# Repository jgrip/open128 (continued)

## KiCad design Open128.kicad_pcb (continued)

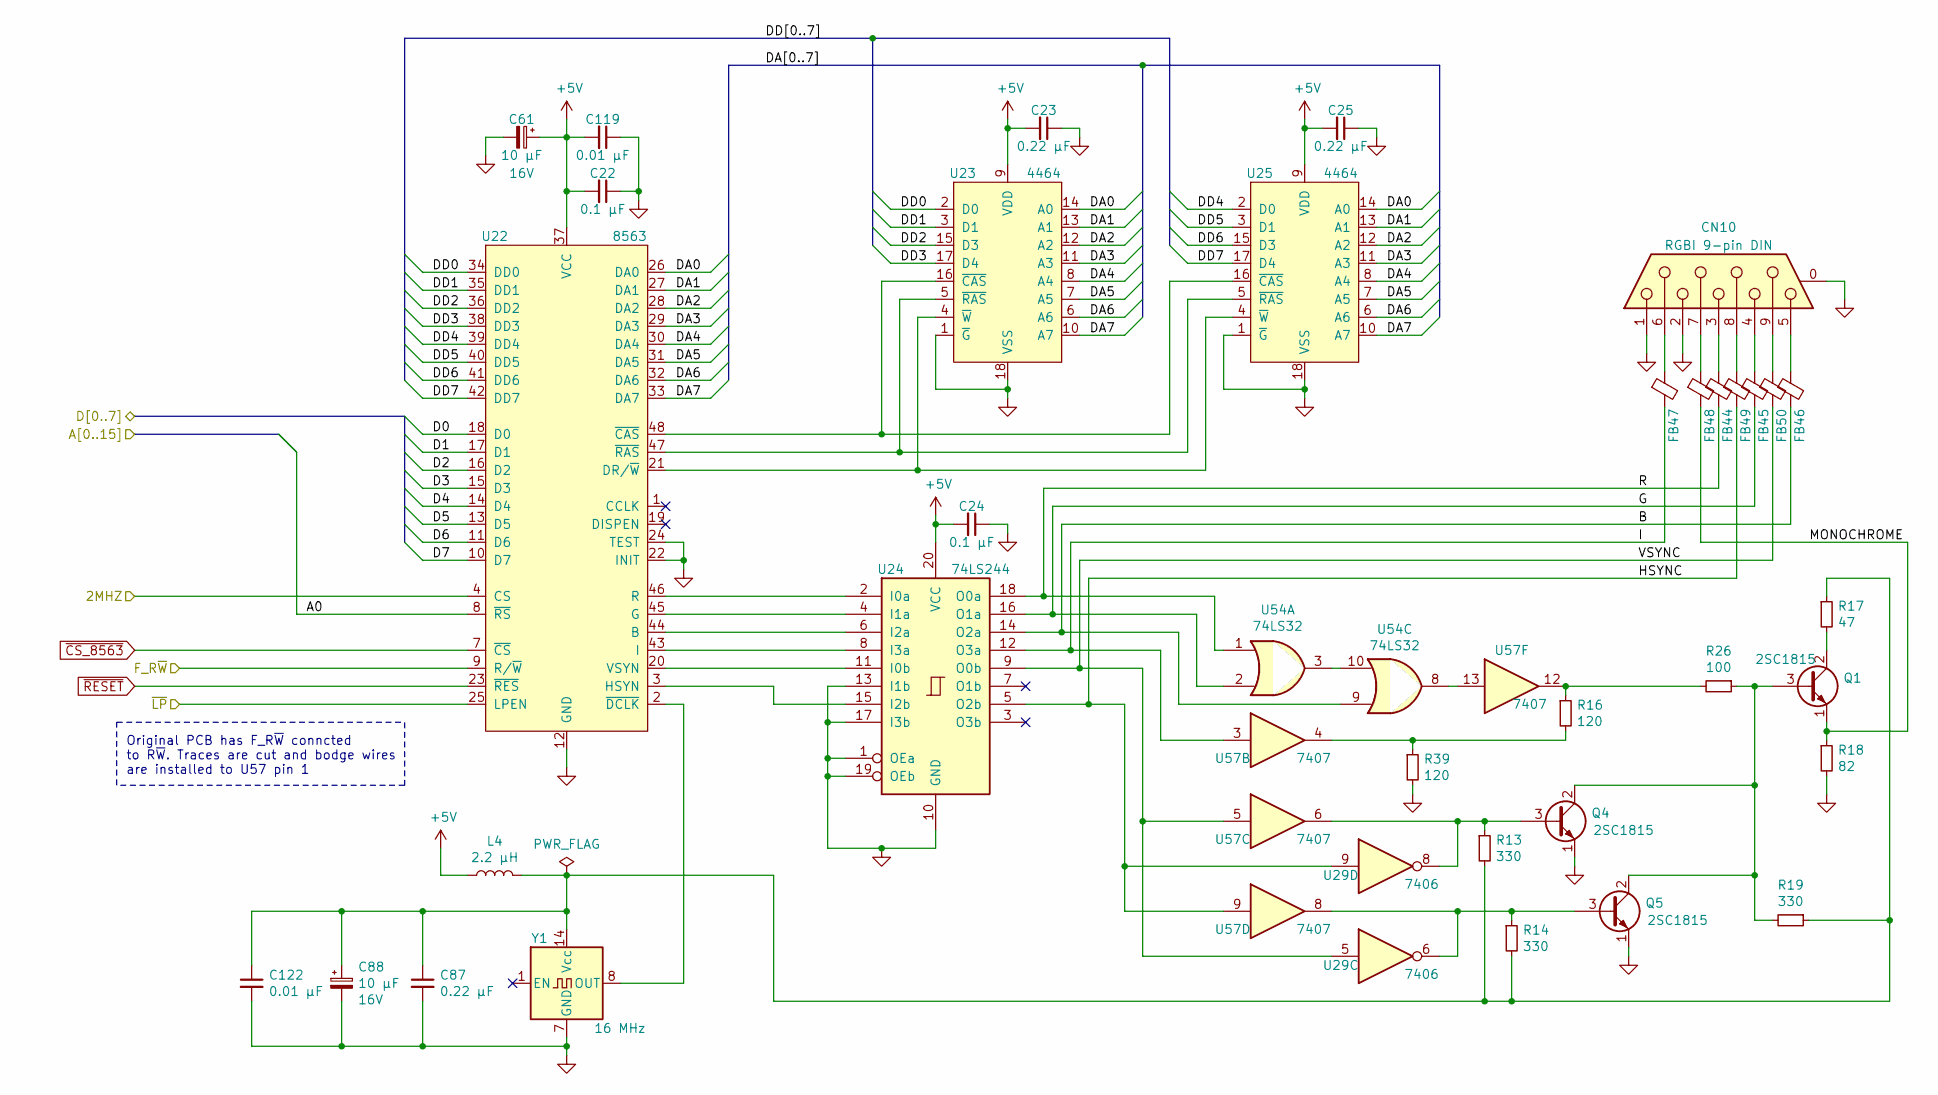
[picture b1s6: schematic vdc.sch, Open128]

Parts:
C22, C24: 0.1 µF; C_Disc_D10.0mm_W2.5mm_P5.00mm; Voltage Rating 25V; Voltage Tolerance +80% -20%; Mouser Part 581-SA105E104MAR
C23, C25, C87: 0.22 µF; C_Disc_D10.0mm_W2.5mm_P5.00mm; Mouser Part 581-SA115E224MAR
C61, C88: 10 µF; CP_Radial_Tantal_D5.0mm_P5.00mm; Voltage Tolerance 16V; Mouser Part 647-UVR1H100MDD1TD
C119, C122: 0.01 µF; C_Disc_D10.0mm_W2.5mm_P5.00mm; Voltage Rating 25V; Voltage Tolerance +80% -20%; Mouser Part 581-SA105E103M
CN10: RGBI 9-pin DIN; DSUB-9_Male_Horizontal_P2.77x2.84mm_EdgePinOffset7.70mm_Hou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; Mouser Part 636-182-009-213R181
FB44, FB45, FB46, FB47, FB48, FB49, FB50: Ferrite_Bead_Small; Ferrite_Bead_vertical; Mouser Part 81-BL02RN2R1M2B
L4: 2.2 µH; L_Axial_L9.5mm_D4.0mm_P12.70mm_Horizontal_Fastron_SMCC; Mouser Part 871-B78108S1222K
Q1, Q4, Q5: 2SC1815; TO-92_Inline_Wide; Mouser Part 512-KSC1815YTA
R13, R14: 330; R_Axial_DIN0411_L9.9mm_D3.6mm_P12.70mm_Horizontal; Mouser Part 660-MF1/2LCT52R331J
R16, R39: 120; R_Axial_DIN0309_L9.0mm_D2.5mm_P12.70mm_Horizontal; Mouser Part 660-MF1/4DCT52R1200F
R17: 47; R_Axial_DIN0309_L9.0mm_D2.5mm_P12.70mm_Horizontal; Mouser Part 660-MF1/4DCT52R47R0F
R18: 82; R_Axial_DIN0309_L9.0mm_D2.5mm_P12.70mm_Horizontal; Mouser Part 660-MF1/4DCT52R82R0F
R19: 330; R_Axial_DIN0309_L9.0mm_D2.5mm_P12.70mm_Horizontal; Mouser Part 660-MF1/2LCT52R331J
R26: 100; R_Axial_DIN0309_L9.0mm_D2.5mm_P12.70mm_Horizontal; Mouser Part 660-MF1/4DCT52A1000F
U22: 8563; DIP-48_W15.24mm_Socket
U23, U25: 4464; DIP-18_W7.62mm_Socket
U24: 74LS244; DIP-20_W7.62mm; Mouser Part 595-SN74LS244N
U29: 7406; DIP-14_W7.62mm; Mouser Part 595-SN74LS06N
U54: 74LS32; DIP-14_W7.62mm; Mouser Part 595-SN74LS32N
U57: 7407; DIP-14_W7.62mm; Mouser Part 595-SN74LS07N
Y1: 16 MHz; Oscillator_DIP-14; Mouser Part 774-MXO45-2C-16M0000

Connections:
+5V: C22.2, C23.2, C24.2, C25.2, C61.1, C119.2, L4.1, U22.37 (VCC), U23.9 (VDD), U24.20 (VCC), U25.9 (VDD); also elsewhere on the board
/Address Multiplexing/A0: U22.8 (~RS); also elsewhere on the board
/CPU 8502/2MHZ: U22.4 (CS); also elsewhere on the board
/CPU 8502/D0: U22.18 (D0); also elsewhere on the board
/CPU 8502/D1: U22.17 (D1); also elsewhere on the board
/CPU 8502/D2: U22.16 (D2); also elsewhere on the board
/CPU 8502/D3: U22.15 (D3); also elsewhere on the board
/CPU 8502/D4: U22.14 (D4); also elsewhere on the board
/CPU 8502/D5: U22.13 (D5); also elsewhere on the board
/CPU 8502/D6: U22.11 (D6); also elsewhere on the board
/CPU 8502/D7: U22.10 (D7); also elsewhere on the board
/CPU 8502/F_R~W: U22.9 (R/~W); also elsewhere on the board
/VDC/B: FB46.2, U24.14 (O2a), U54.9
/VDC/DA0: U22.26 (DA0), U23.14 (A0), U25.14 (A0)
/VDC/DA1: U22.27 (DA1), U23.13 (A1), U25.13 (A1)
/VDC/DA2: U22.28 (DA2), U23.12 (A2), U25.12 (A2)
/VDC/DA3: U22.29 (DA3), U23.11 (A3), U25.11 (A3)
/VDC/DA4: U22.30 (DA4), U23.8 (A4), U25.8 (A4)
/VDC/DA5: U22.31 (DA5), U23.7 (A5), U25.7 (A5)
/VDC/DA6: U22.32 (DA6), U23.6 (A6), U25.6 (A6)
/VDC/DA7: U22.33 (DA7), U23.10 (A7), U25.10 (A7)
/VDC/DD0: U22.34 (DD0), U23.2 (D0)
/VDC/DD1: U22.35 (DD1), U23.3 (D1)
/VDC/DD2: U22.36 (DD2), U23.15 (D3)
/VDC/DD3: U22.38 (DD3), U23.17 (D4)
/VDC/DD4: U22.39 (DD4), U25.2 (D0)
/VDC/DD5: U22.40 (DD5), U25.3 (D1)
/VDC/DD6: U22.41 (DD6), U25.15 (D3)
/VDC/DD7: U22.42 (DD7), U25.17 (D4)
/VDC/G: FB45.2, U24.16 (O1a), U54.2
/VDC/HSYNC: FB49.2, U24.5 (O2b), U29.9, U57.9
/VDC/I: FB47.2, U24.12 (O3a), U57.3
/VDC/MONOCHROME: FB48.2, Q1.1 (E), R18.1
/VDC/R: FB44.2, U24.18 (O0a), U54.1
/VDC/VSYNC: FB50.2, U24.9 (O0b), U29.5, U57.5
/VIC/~LIGHTPEN: U22.25 (LPEN); also elsewhere on the board
GND: C22.1, C23.1, C24.1, C25.1, C61.2, C87.2, C88.2, C119.1, C122.2, CN10.0 (PAD), CN10.1, CN10.2, FB44.3 (GND), FB45.3 (GND), FB46.3 (GND), FB47.3 (GND), FB48.3 (GND), FB49.3 (GND), FB50.3 (GND), Q4.1 (E), Q5.1 (E), R18.2, R39.2, U22.12 (GND), U22.22 (INIT), U22.24 (TEST), U23.1 (~G), U23.18 (VSS), U24.1 (OEa), U24.10 (GND), U24.13 (I1b), U24.17 (I3b), U24.19 (OEb), U25.1 (~G), U25.18 (VSS), Y1.7 (GND); also elsewhere on the board
unnamed: C87.1, C88.1, C122.1, L4.2, R13.2, R14.2, R17.1, R19.1, Y1.14 (Vcc)
unnamed: CN10.3, FB44.1
unnamed: CN10.4, FB45.1
unnamed: CN10.5, FB46.1
unnamed: CN10.6, FB47.1
unnamed: CN10.7, FB48.1
unnamed: CN10.8, FB49.1
unnamed: CN10.9, FB50.1
unnamed: Q1.2 (C), R17.2
unnamed: Q1.3 (B), Q4.2 (C), Q5.2 (C), R19.2, R26.1
unnamed: Q4.3 (B), R13.1, U29.8, U57.6
unnamed: Q5.3 (B), R14.1, U29.6, U57.8
unnamed: R16.1, R26.2, U57.12
unnamed: R16.2, R39.1, U57.4
unnamed: U22.2 (~DCLK), Y1.8 (OUT)
unnamed: U22.3 (HSYN), U24.15 (I2b)
unnamed: U22.20 (VSYN), U24.11 (I0b)
unnamed: U22.21 (DR/~W), U23.4 (~W), U25.4 (~W)
unnamed: U22.43 (I), U24.8 (I3a)
unnamed: U22.44 (B), U24.6 (I2a)
unnamed: U22.45 (G), U24.4 (I1a)
unnamed: U22.46 (R), U24.2 (I0a)
unnamed: U22.47 (~RAS), U23.5 (~RAS), U25.5 (~RAS)
unnamed: U22.48 (~CAS), U23.16 (~CAS), U25.16 (~CAS)
unnamed: U54.8, U57.13
unnamed: U54.3, U54.10
~CS_8563: U22.7 (~CS); also elsewhere on the board
~RESET: U22.23 (~RES); also elsewhere on the board

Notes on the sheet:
Original PCB has F_R~W~ conncted to R~W~. Traces are cut and bodge wires are installed to U57 pin 1

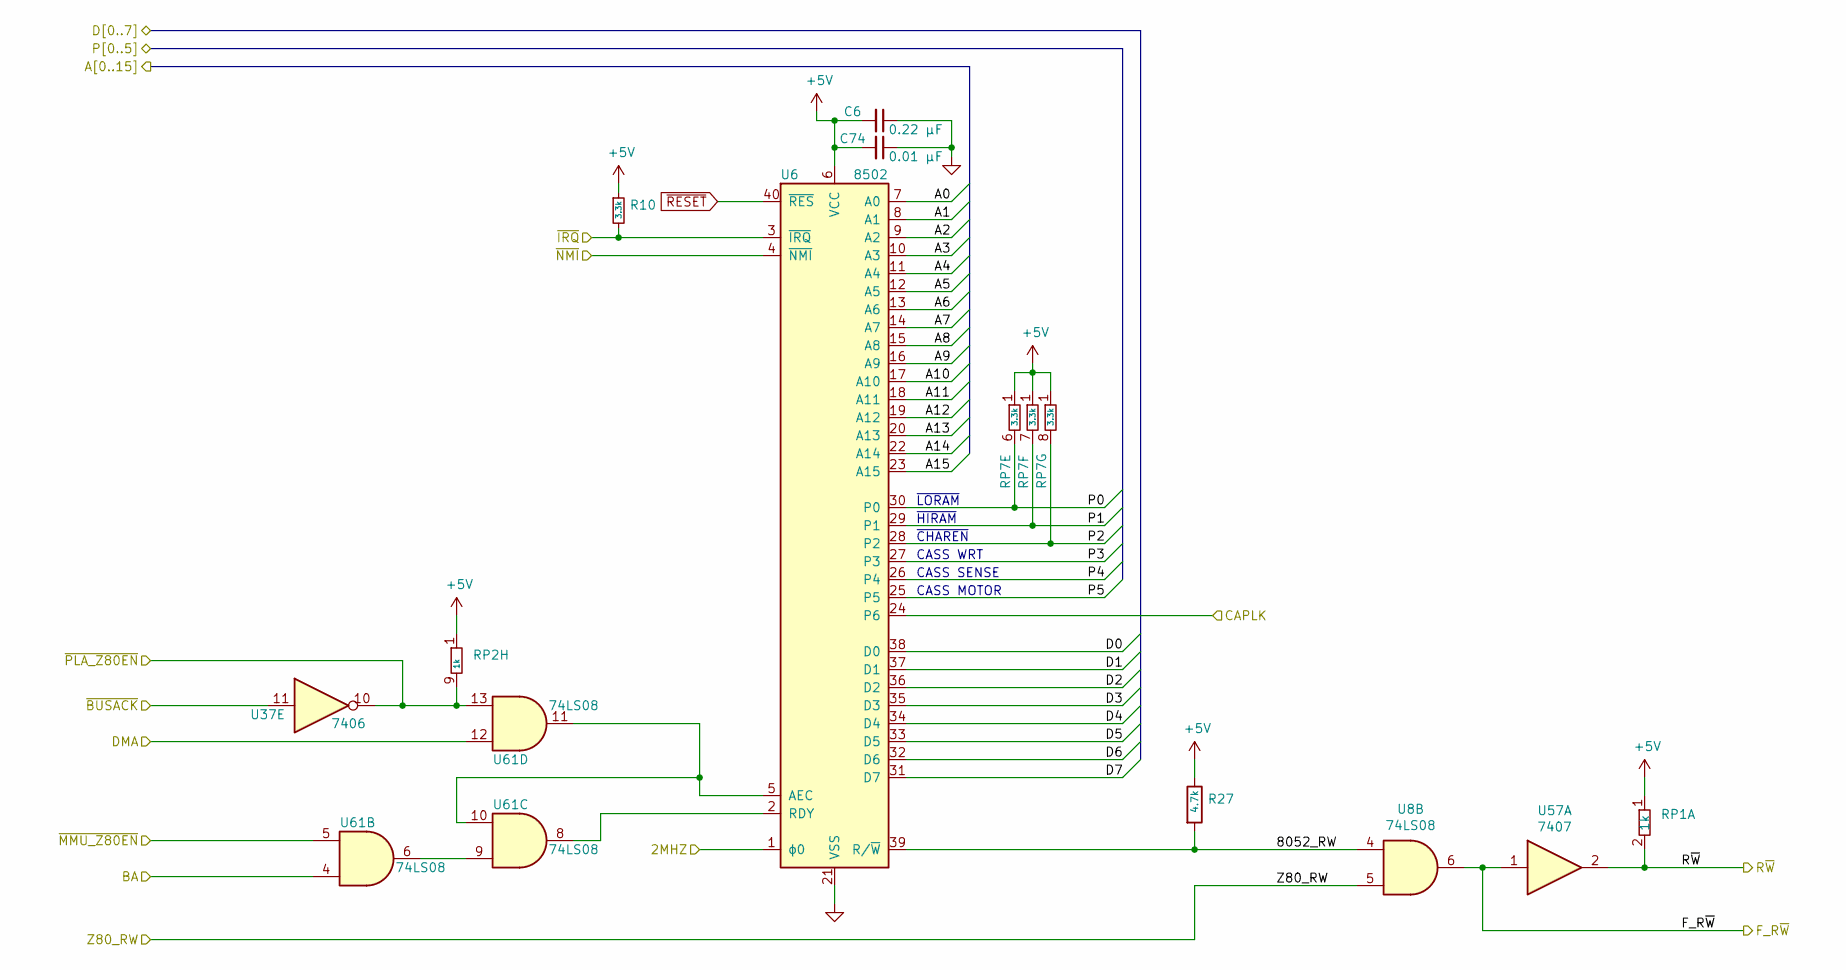
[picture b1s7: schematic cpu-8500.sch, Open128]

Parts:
C6: 0.22 µF; C_Disc_D10.0mm_W2.5mm_P5.00mm; Mouser Part 581-SA115E224MAR
C74: 0.01 µF; C_Disc_D10.0mm_W2.5mm_P5.00mm; Voltage Rating 25V; Voltage Tolerance +80% -20%; Mouser Part 581-SA105E103M
R10: 3.3k; R_Axial_DIN0309_L9.0mm_D2.5mm_P12.70mm_Horizontal; Mouser Part 660-MF1/4LCT52R332J
R27: 4.7k; R_Axial_DIN0309_L9.0mm_D2.5mm_P12.70mm_Horizontal; Mouser Part 660-MF1/4LCT52R472J
RP1: 1k; R_Array_SIP8; Mouser Part 652-4608X-1LF-1K
RP2: 1k; R_Array_SIP9; Mouser Part 652-4609X-1LF-1K
RP7: 3.3k; R_Array_SIP10; Mouser Part 652-4610X-1LF-3.3K
U6: 8502; DIP-40_W15.24mm_Socket
U8, U61: 74LS08; DIP-14_W7.62mm; Mouser Part 595-SN74LS08N
U37: 7406; DIP-14_W7.62mm; Mouser Part 595-SN74LS06N
U57: 7407; DIP-14_W7.62mm; Mouser Part 595-SN74LS07N

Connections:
+5V: C6.2, C74.2, R10.1, R27.1, RP1.1 (common), RP2.1 (common), RP7.1 (common), U6.6 (VCC); also elsewhere on the board
/Address Multiplexing/A0: U6.7 (A0); also elsewhere on the board
/Address Multiplexing/A1: U6.8 (A1); also elsewhere on the board
/Address Multiplexing/A2: U6.9 (A2); also elsewhere on the board
/Address Multiplexing/A3: U6.10 (A3); also elsewhere on the board
/Address Multiplexing/A4: U6.11 (A4); also elsewhere on the board
/Address Multiplexing/A5: U6.12 (A5); also elsewhere on the board
/Address Multiplexing/A6: U6.13 (A6); also elsewhere on the board
/Address Multiplexing/A7: U6.14 (A7); also elsewhere on the board
/Address Multiplexing/A8: U6.15 (A8); also elsewhere on the board
/Address Multiplexing/A9: U6.16 (A9); also elsewhere on the board
/Address Multiplexing/A10: U6.17 (A10); also elsewhere on the board
/Address Multiplexing/A11: U6.18 (A11); also elsewhere on the board
/Address Multiplexing/A12: U6.19 (A12); also elsewhere on the board
/Address Multiplexing/A13: U6.20 (A13); also elsewhere on the board
/Address Multiplexing/A14: U6.22 (A14); also elsewhere on the board
/Address Multiplexing/A15: U6.23 (A15); also elsewhere on the board
/BA: U61.4; also elsewhere on the board
/CPU 8502/2MHZ: U6.1 (ϕ0); also elsewhere on the board
/CPU 8502/8052_RW: R27.2, U6.39 (R/~W), U8.4
/CPU 8502/CAPLK: U6.24 (P6); also elsewhere on the board
/CPU 8502/D0: U6.38 (D0); also elsewhere on the board
/CPU 8502/D1: U6.37 (D1); also elsewhere on the board
/CPU 8502/D2: U6.36 (D2); also elsewhere on the board
/CPU 8502/D3: U6.35 (D3); also elsewhere on the board
/CPU 8502/D4: U6.34 (D4); also elsewhere on the board
/CPU 8502/D5: U6.33 (D5); also elsewhere on the board
/CPU 8502/D6: U6.32 (D6); also elsewhere on the board
/CPU 8502/D7: U6.31 (D7); also elsewhere on the board
/CPU 8502/DMA: U61.12; also elsewhere on the board
/CPU 8502/F_R~W: U8.6, U57.1; also elsewhere on the board
/CPU 8502/P0: RP7.6 (R5), U6.30 (P0); also elsewhere on the board
/CPU 8502/P1: RP7.7 (R6), U6.29 (P1); also elsewhere on the board
/CPU 8502/P2: RP7.8 (R7), U6.28 (P2); also elsewhere on the board
/CPU 8502/P3: U6.27 (P3); also elsewhere on the board
/CPU 8502/P4: U6.26 (P4); also elsewhere on the board
/CPU 8502/P5: U6.25 (P5); also elsewhere on the board
/CPU 8502/Z80_RW: U8.5; also elsewhere on the board
/CPU 8502/~BUSACK: U37.11; also elsewhere on the board
/CPU 8502/~MMU_Z80EN: U61.5; also elsewhere on the board
/CPU 8502/~NMI: U6.4 (~NMI); also elsewhere on the board
/Memory Management/~BUSACK: RP2.9 (R8), U37.10, U61.13; also elsewhere on the board
/R~W: RP1.2 (R1), U57.2; also elsewhere on the board
/~IRQ: R10.2, U6.3 (~IRQ); also elsewhere on the board
GND: C6.1, C74.1, U6.21 (VSS); also elsewhere on the board
unnamed: U6.2 (RDY), U61.8
unnamed: U6.5 (AEC), U61.10, U61.11
unnamed: U61.6, U61.9
~RESET: U6.40 (~RES); also elsewhere on the board

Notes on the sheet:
~LORAM
~HIRAM
~CHAREN
CASS WRT
CASS SENSE
CASS MOTOR

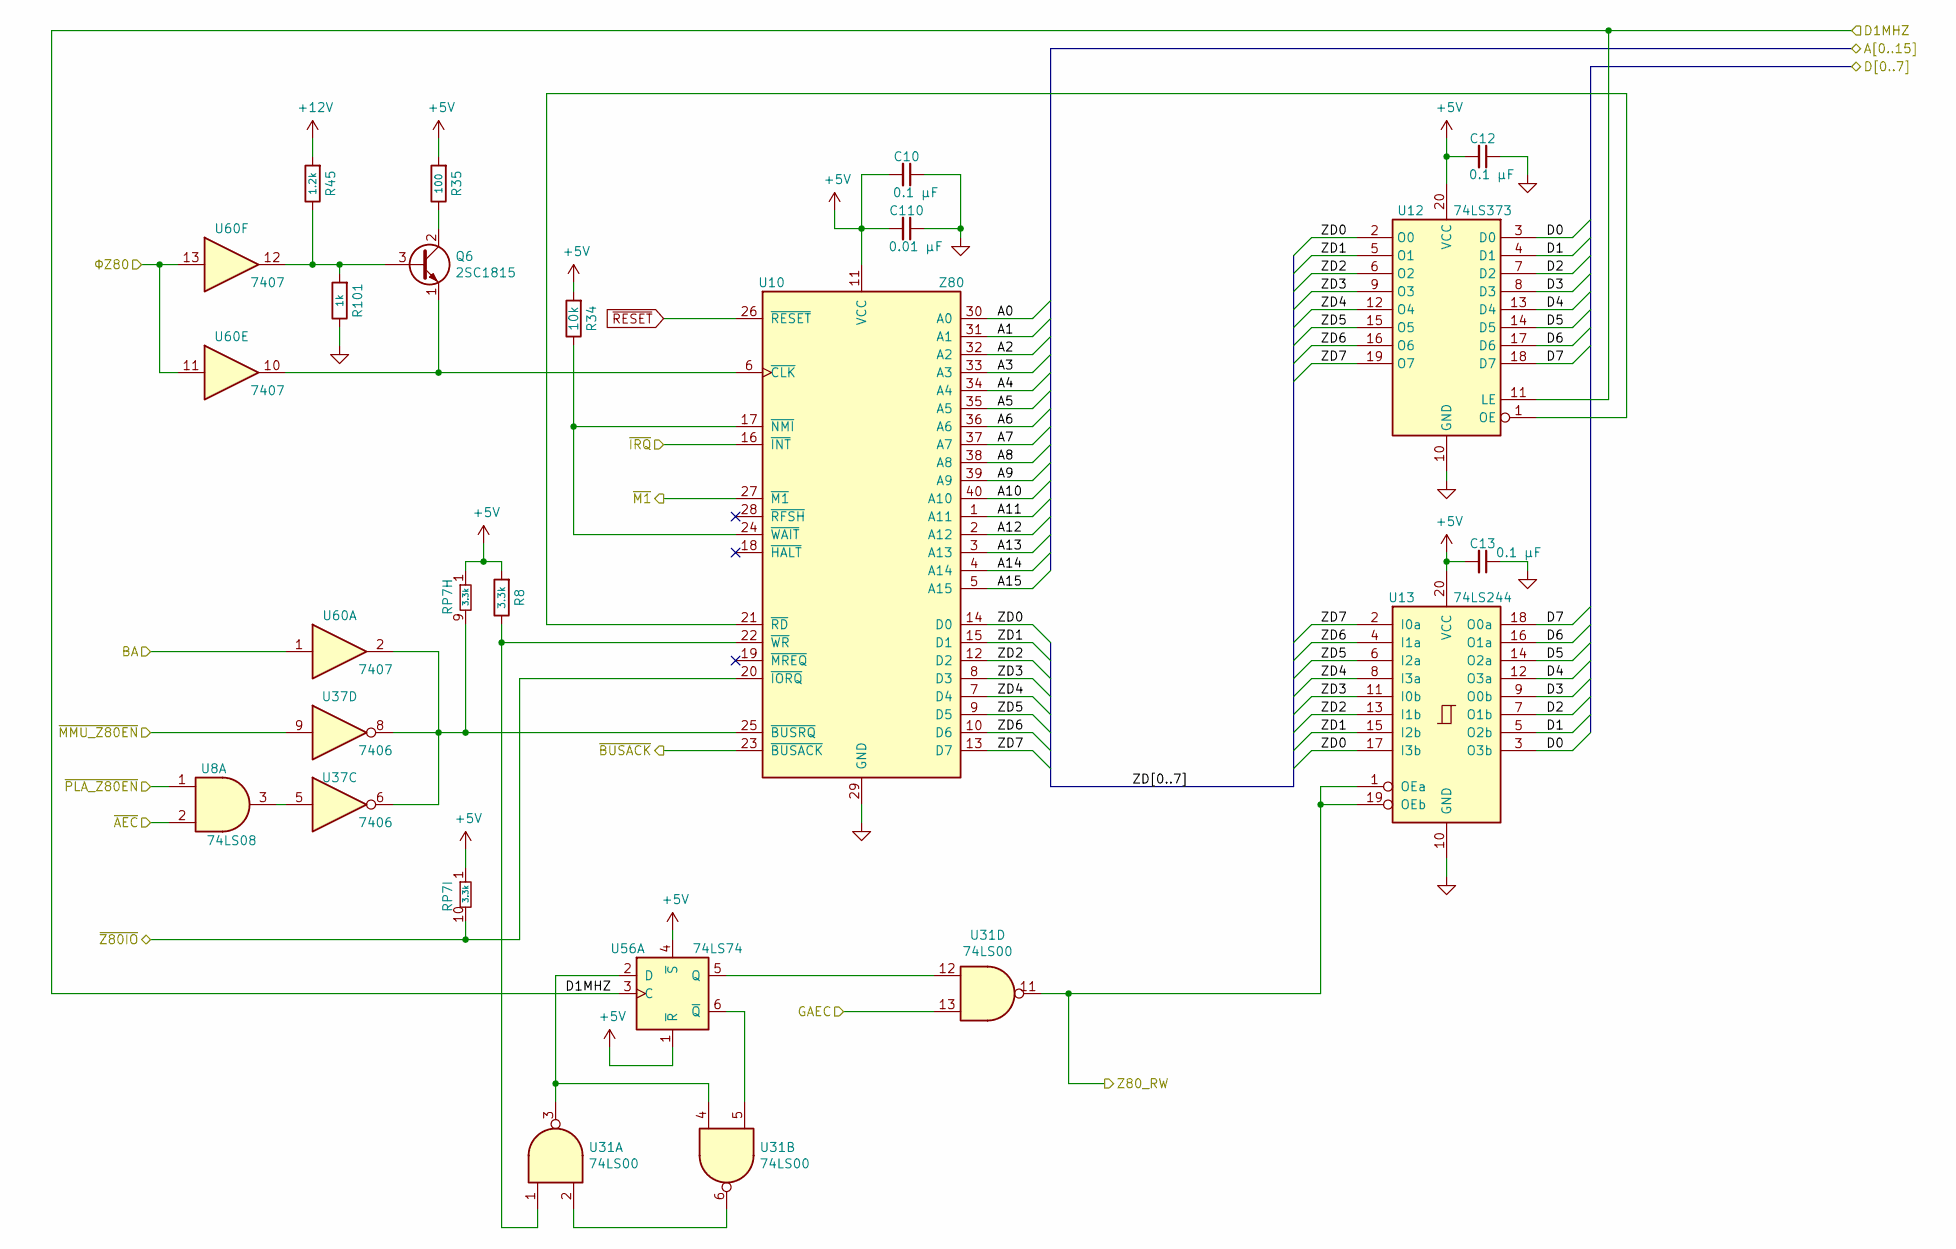
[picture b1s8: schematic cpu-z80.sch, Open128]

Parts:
C10, C12, C13: 0.1 µF; C_Disc_D10.0mm_W2.5mm_P5.00mm; Voltage Rating 25V; Voltage Tolerance +80% -20%; Mouser Part 581-SA105E104MAR
C110: 0.01 µF; C_Disc_D10.0mm_W2.5mm_P5.00mm; Voltage Rating 25V; Voltage Tolerance +80% -20%; Mouser Part 581-SA105E103M
Q6: 2SC1815; TO-92_Inline_Wide; Mouser Part 512-KSC1815YTA
R8: 3.3k; R_Axial_DIN0309_L9.0mm_D2.5mm_P12.70mm_Horizontal; Mouser Part 660-MF1/4LCT52R332J
R34: 10k; R_Axial_DIN0309_L9.0mm_D2.5mm_P12.70mm_Horizontal; Mouser Part 660-MF1/4LCT52R103J
R35: 100; R_Axial_DIN0309_L9.0mm_D2.5mm_P12.70mm_Horizontal; Mouser Part 660-MF1/4DCT52A1000F
R45: 1.2k; R_Axial_DIN0309_L9.0mm_D2.5mm_P12.70mm_Horizontal; Mouser Part 660-MF1/4LCT52R122J
R101: 1k; R_Axial_DIN0309_L9.0mm_D2.5mm_P12.70mm_Horizontal; Mouser Part 660-MF1/4LCT52R102J
RP7: 3.3k; R_Array_SIP10; Mouser Part 652-4610X-1LF-3.3K
U8: 74LS08; DIP-14_W7.62mm; Mouser Part 595-SN74LS08N
U10: Z80; DIP-40_W15.24mm_Socket
U12: 74LS373; DIP-20_W7.62mm; Mouser Part 595-SN74LS373N
U13: 74LS244; DIP-20_W7.62mm; Mouser Part 595-SN74LS244N
U31: 74LS00; DIP-14_W7.62mm; Mouser Part 595-SN74LS00N
U37: 7406; DIP-14_W7.62mm; Mouser Part 595-SN74LS06N
U56: 74LS74; DIP-14_W7.62mm; Mouser Part 595-SN74LS74AN
U60: 7407; DIP-14_W7.62mm; Mouser Part 595-SN74LS07N

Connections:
+5V: C10.2, C12.2, C13.2, C110.2, R8.2, R34.2, R35.2, RP7.1 (common), U10.11 (VCC), U12.20 (VCC), U13.20 (VCC), U56.1 (~R), U56.4 (~S); also elsewhere on the board
+12V: R45.2; also elsewhere on the board
/Address Multiplexing/A0: U10.30 (A0); also elsewhere on the board
/Address Multiplexing/A1: U10.31 (A1); also elsewhere on the board
/Address Multiplexing/A2: U10.32 (A2); also elsewhere on the board
/Address Multiplexing/A3: U10.33 (A3); also elsewhere on the board
/Address Multiplexing/A4: U10.34 (A4); also elsewhere on the board
/Address Multiplexing/A5: U10.35 (A5); also elsewhere on the board
/Address Multiplexing/A6: U10.36 (A6); also elsewhere on the board
/Address Multiplexing/A7: U10.37 (A7); also elsewhere on the board
/Address Multiplexing/A8: U10.38 (A8); also elsewhere on the board
/Address Multiplexing/A9: U10.39 (A9); also elsewhere on the board
/Address Multiplexing/A10: U10.40 (A10); also elsewhere on the board
/Address Multiplexing/A11: U10.1 (A11); also elsewhere on the board
/Address Multiplexing/A12: U10.2 (A12); also elsewhere on the board
/Address Multiplexing/A13: U10.3 (A13); also elsewhere on the board
/Address Multiplexing/A14: U10.4 (A14); also elsewhere on the board
/Address Multiplexing/A15: U10.5 (A15); also elsewhere on the board
/Address Multiplexing/~AEC: U8.2; also elsewhere on the board
/BA: U60.1; also elsewhere on the board
/CPU 8502/D0: U12.3 (D0), U13.3 (O3b); also elsewhere on the board
/CPU 8502/D1: U12.4 (D1), U13.5 (O2b); also elsewhere on the board
/CPU 8502/D2: U12.7 (D2), U13.7 (O1b); also elsewhere on the board
/CPU 8502/D3: U12.8 (D3), U13.9 (O0b); also elsewhere on the board
/CPU 8502/D4: U12.13 (D4), U13.12 (O3a); also elsewhere on the board
/CPU 8502/D5: U12.14 (D5), U13.14 (O2a); also elsewhere on the board
/CPU 8502/D6: U12.17 (D6), U13.16 (O1a); also elsewhere on the board
/CPU 8502/D7: U12.18 (D7), U13.18 (O0a); also elsewhere on the board
/CPU 8502/Z80_RW: U13.1 (OEa), U13.19 (OEb), U31.11; also elsewhere on the board
/CPU 8502/~BUSACK: U10.23 (~BUSACK~); also elsewhere on the board
/CPU 8502/~MMU_Z80EN: U37.9; also elsewhere on the board
/CPU Z80/D1MHZ: U12.11 (LE), U56.3 (C); also elsewhere on the board
/CPU Z80/GAEC: U31.13; also elsewhere on the board
/CPU Z80/ZD0: U10.14 (D0), U12.2 (O0), U13.17 (I3b)
/CPU Z80/ZD1: U10.15 (D1), U12.5 (O1), U13.15 (I2b)
/CPU Z80/ZD2: U10.12 (D2), U12.6 (O2), U13.13 (I1b)
/CPU Z80/ZD3: U10.8 (D3), U12.9 (O3), U13.11 (I0b)
/CPU Z80/ZD4: U10.7 (D4), U12.12 (O4), U13.8 (I3a)
/CPU Z80/ZD5: U10.9 (D5), U12.15 (O5), U13.6 (I2a)
/CPU Z80/ZD6: U10.10 (D6), U12.16 (O6), U13.4 (I1a)
/CPU Z80/ZD7: U10.13 (D7), U12.19 (O7), U13.2 (I0a)
/CPU Z80/~Z80IO: RP7.10 (R9), U10.20 (~IORQ~); also elsewhere on the board
/CPU Z80/ΦZ80: U60.11, U60.13; also elsewhere on the board
/Memory Management/M1: U10.27 (~M1~); also elsewhere on the board
/Memory Management/~BUSACK: U8.1; also elsewhere on the board
/~IRQ: U10.16 (~INT~); also elsewhere on the board
GND: C10.1, C12.1, C13.1, C110.1, R101.1, U10.29 (GND), U12.10 (GND), U13.10 (GND); also elsewhere on the board
unnamed: Q6.1 (E), U10.6 (~CLK~), U60.10
unnamed: Q6.2 (C), R35.1
unnamed: Q6.3 (B), R45.1, R101.2, U60.12
unnamed: R8.1, U10.22 (~WR~), U31.1
unnamed: R34.1, U10.17 (~NMI~), U10.24 (~WAIT~)
unnamed: RP7.9 (R8), U10.25 (~BUSRQ~), U37.6, U37.8, U60.2
unnamed: U10.21 (~RD~), U12.1 (OE)
unnamed: U31.2, U31.6
unnamed: U31.3, U31.4, U56.2 (D)
unnamed: U31.5, U56.6 (~Q)
unnamed: U31.12, U56.5 (Q)
unnamed: U8.3, U37.5
~RESET: U10.26 (~RESET~); also elsewhere on the board

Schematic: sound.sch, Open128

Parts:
C5, C86: 0.1 µF; C_Disc_D10.0mm_W2.5mm_P5.00mm; Voltage Rating 25V; Voltage Tolerance +80% -20%; Mouser Part 581-SA105E104MAR
C81: 1000 pF; C_Disc_D10.0mm_W2.5mm_P5.00mm; Voltage Rating 50V; Voltage Tolerance 10%; Mouser Part 581-SA101C102KAN
C82, C83, C112: 470 pF; C_Disc_D10.0mm_W2.5mm_P5.00mm; Mouser Part 581-SA101A471JAR
C84: 220 pF; C_Disc_D10.0mm_W2.5mm_P5.00mm; Mouser Part 581-SA102C221KAA
C85: 10 µF; CP_Radial_Tantal_D5.0mm_P5.00mm; Voltage Tolerance 16V; Mouser Part 647-UVR1H100MDD1TD
C108, C109: 1800 pF; C_Disc_D10.0mm_W2.5mm_P5.00mm; Mouser Part 581-SA101C182KAR
Q2: 2SC1815; TO-92_Inline_Wide; Mouser Part 512-KSC1815YTA
R6: 47k; R_Axial_DIN0309_L9.0mm_D2.5mm_P12.70mm_Horizontal; Mouser Part 660-MF1/4LCT52R473J
R11, R12: 1k; R_Axial_DIN0309_L9.0mm_D2.5mm_P12.70mm_Horizontal; Mouser Part 660-MF1/4LCT52R102J
R28: 10k; R_Axial_DIN0309_L9.0mm_D2.5mm_P12.70mm_Horizontal; Mouser Part 660-MF1/4LCT52R103J
U5: 6581; DIP-28_W15.24mm_Socket

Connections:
+5V: C5.2, U5.25 (VCC); also elsewhere on the board
+12V: C86.2, Q2.2 (C), U5.28 (VDD); also elsewhere on the board
/Address Multiplexing/A0: U5.9 (A0); also elsewhere on the board
/Address Multiplexing/A1: U5.10 (A1); also elsewhere on the board
/Address Multiplexing/A2: U5.11 (A2); also elsewhere on the board
/Address Multiplexing/A3: U5.12 (A3); also elsewhere on the board
/Address Multiplexing/A4: U5.13 (A4); also elsewhere on the board
/CPU 8502/D0: U5.15 (D0); also elsewhere on the board
/CPU 8502/D1: U5.16 (D1); also elsewhere on the board
/CPU 8502/D2: U5.17 (D2); also elsewhere on the board
/CPU 8502/D3: U5.18 (D3); also elsewhere on the board
/CPU 8502/D4: U5.19 (D4); also elsewhere on the board
/CPU 8502/D5: U5.20 (D5); also elsewhere on the board
/CPU 8502/D6: U5.21 (D6); also elsewhere on the board
/CPU 8502/D7: U5.22 (D7); also elsewhere on the board
/Expansion Port/1MHZ: U5.6 (ϕ2); also elsewhere on the board
/I/O/POTX: C108.2, U5.24 (POTX); also elsewhere on the board
/I/O/POTY: C109.2, U5.23 (POTY); also elsewhere on the board
/R~W: U5.7 (R/~W); also elsewhere on the board
/Sound/AUDIO_OUT: C85.2, R6.1; also elsewhere on the board
/Sound/EXT_AUDIO: U5.26 (EXT_IN); also elsewhere on the board
GND: C5.1, C81.1, C84.1, C86.1, C108.1, C109.1, R6.2, R11.2, R12.2, U5.14 (GND); also elsewhere on the board
unnamed: C82.1, U5.4 (CAP2B)
unnamed: C82.2, U5.3 (CAP2A)
unnamed: C83.1, U5.2 (CAP1B)
unnamed: C83.2, U5.1 (CAP1A)
unnamed: C81.2, C112.1, Q2.3 (B), R28.1
unnamed: C84.2, C85.1, C112.2, Q2.1 (E), R12.1
unnamed: R11.1, R28.2, U5.27 (AUDIO_OUT)
~CS_SID: U5.8 (~CS); also elsewhere on the board
~RESET: U5.5 (~RES); also elsewhere on the board

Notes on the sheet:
Replace +12V with UNREG +9V if 8580 is used.

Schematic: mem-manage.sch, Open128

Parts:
C2, C77: 0.01 µF; C_Disc_D10.0mm_W2.5mm_P5.00mm; Voltage Rating 25V; Voltage Tolerance +80% -20%; Mouser Part 581-SA105E103M
C3, C7, C11: 0.1 µF; C_Disc_D10.0mm_W2.5mm_P5.00mm; Voltage Rating 25V; Voltage Tolerance +80% -20%; Mouser Part 581-SA105E104MAR
J2, J3: Close to enable CAS latch; PinHeader_1x02_P2.54mm_Vertical
R33: 10k; R_Axial_DIN0309_L9.0mm_D2.5mm_P12.70mm_Horizontal; Mouser Part 660-MF1/4LCT52R103J
U3: 74LS138; DIP-16_W7.62mm; Mouser Part 595-SN74LS138N
U7: 8722; DIP-48_W15.24mm_Socket
U9: 74F32; DIP-14_W7.62mm; Mouser Part 595-SN74F32N
U11: 8721; DIP-48_W15.24mm_Socket
U31: 74LS00; DIP-14_W7.62mm; Mouser Part 595-SN74LS00N
U54: 74LS32; DIP-14_W7.62mm; Mouser Part 595-SN74LS32N
U61: 74LS08; DIP-14_W7.62mm; Mouser Part 595-SN74LS08N

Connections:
+5V: C2.1, C3.2, C7.1, C11.2, C77.2, R33.1, U3.6 (E3), U3.16 (VCC), U7.1 (VCC), U11.8 (DMAACK), U11.48 (VCC); also elsewhere on the board
/AEC: U11.9 (AEC), U61.2; also elsewhere on the board
/Address Multiplexing/A0: U7.18 (A0); also elsewhere on the board
/Address Multiplexing/A1: U7.19 (A1); also elsewhere on the board
/Address Multiplexing/A2: U7.20 (A2); also elsewhere on the board
/Address Multiplexing/A3: U7.21 (A3); also elsewhere on the board
/Address Multiplexing/A4: U54.13; also elsewhere on the board
/Address Multiplexing/A5: U54.12; also elsewhere on the board
/Address Multiplexing/A6: U54.5; also elsewhere on the board
/Address Multiplexing/A7: U54.4; also elsewhere on the board
/Address Multiplexing/A8: U3.1 (A0), U7.24 (A8); also elsewhere on the board
/Address Multiplexing/A9: U3.2 (A1), U7.25 (A9); also elsewhere on the board
/Address Multiplexing/A10: U7.26 (A10), U11.6 (A10), U31.9; also elsewhere on the board
/Address Multiplexing/A11: U3.3 (A2), U7.27 (A11), U11.5 (A11); also elsewhere on the board
/Address Multiplexing/A12: U7.28 (A12), U11.4 (A12); also elsewhere on the board
/Address Multiplexing/A13: U7.29 (A13), U11.3 (A13); also elsewhere on the board
/Address Multiplexing/A14: U7.30 (A14), U11.2 (A14); also elsewhere on the board
/Address Multiplexing/A15: U7.31 (A15), U11.1 (A15); also elsewhere on the board
/Address Multiplexing/MUX: U7.17 (MUX); also elsewhere on the board
/Address Multiplexing/TA8: U7.10 (TA8); also elsewhere on the board
/Address Multiplexing/TA9: U7.9 (TA9); also elsewhere on the board
/Address Multiplexing/TA10: U7.8 (TA10); also elsewhere on the board
/Address Multiplexing/TA11: U7.7 (TA11); also elsewhere on the board
/Address Multiplexing/TA12: U7.6 (TA12); also elsewhere on the board
/Address Multiplexing/TA13: U7.5 (TA13); also elsewhere on the board
/Address Multiplexing/TA14: U7.4 (TA14); also elsewhere on the board
/Address Multiplexing/TA15: U7.3 (TA15); also elsewhere on the board
/Address Multiplexing/VMA4: U11.19 (VMA4); also elsewhere on the board
/Address Multiplexing/VMA5: U11.20 (VMA5); also elsewhere on the board
/BA: U11.21 (BA); also elsewhere on the board
/CPU 8502/2MHZ: U7.33 (ΦIN); also elsewhere on the board
/CPU 8502/D0: U7.35 (D0); also elsewhere on the board
/CPU 8502/D1: U7.36 (D1); also elsewhere on the board
/CPU 8502/D2: U7.37 (D2); also elsewhere on the board
/CPU 8502/D3: U7.38 (D3); also elsewhere on the board
/CPU 8502/D4: U7.39 (D4); also elsewhere on the board
/CPU 8502/D5: U7.40 (D5); also elsewhere on the board
/CPU 8502/D6: U7.41 (D6); also elsewhere on the board
/CPU 8502/D7: U7.42 (D7); also elsewhere on the board
/CPU 8502/DMA: U61.1; also elsewhere on the board
/CPU 8502/P0: U11.22 (LORAM); also elsewhere on the board
/CPU 8502/P1: U11.23 (HIRAM); also elsewhere on the board
/CPU 8502/P2: U11.25 (CHAREN); also elsewhere on the board
/CPU 8502/~MMU_Z80EN: U7.43 (~Z80EN); also elsewhere on the board
/CPU Z80/GAEC: U7.16 (AEC), U61.3; also elsewhere on the board
/CPU Z80/~Z80IO: U11.14 (Z80_I/O); also elsewhere on the board
/DRAM/~CAS: U11.47 (CLK); also elsewhere on the board
/DRAM/~DWE: U11.40 (~DWE); also elsewhere on the board
/DRAM/~GCAS0: U9.3; also elsewhere on the board
/DRAM/~GCAS1: U9.6; also elsewhere on the board
/Expansion Port/~EXROM: U7.46 (~EXROM), U11.12 (~EXROM); also elsewhere on the board
/Expansion Port/~GAME: U7.45 (~GAME), U11.11 (~GAME); also elsewhere on the board
/I/O/128_64: U7.47 (MS3), U11.15 (MS3); also elsewhere on the board
/I/O/4080: U7.48 (40/80); also elsewhere on the board
/I/O/~VA14: U11.26 (~VA14); also elsewhere on the board
/Memory Management/CLRBNK: U11.32 (CLRBNK); also elsewhere on the board
/Memory Management/FSDIR: U7.44 (FSDIR); also elsewhere on the board
/Memory Management/IOSEL: U7.13 (MS2), U11.16 (MS2)
/Memory Management/M1: U31.10; also elsewhere on the board
/Memory Management/ROMBANKHI: U7.14 (MS1), U11.17 (MS1)
/Memory Management/ROMBANKLO: U7.15 (MS0), U11.18 (MS0)
/Memory Management/~BUSACK: U11.13 (~Z80EN); also elsewhere on the board
/Memory Management/~GWE: U11.44 (~GWE); also elsewhere on the board
/Memory Management/~IOACC: U11.43 (~IOACC); also elsewhere on the board
/Memory Management/~IO_CS: U3.5 (E2), U11.38 (~I/O_CS)
/R~W: U7.32 (R/~W), U11.10 (R/~W); also elsewhere on the board
GND: C2.2, C3.1, C7.2, C11.1, C77.1, J2.1 (A), J3.2 (B), U3.8 (GND), U7.34 (GND), U11.24 (GND); also elsewhere on the board
unnamed: J2.2 (B), U11.7 (VICFIX)
unnamed: J3.1 (A), R33.2, U11.27 (128/256)
unnamed: U3.4 (E1), U31.8
unnamed: U7.11 (~CAS1), U9.5
unnamed: U7.12 (~CAS0), U9.2
unnamed: U9.1, U9.4, U11.41 (CASENB)
unnamed: U7.23 (A6/7), U54.6
unnamed: U7.22 (A4/5), U54.11
~CS_8563: U3.13 (O2); also elsewhere on the board
~CS_CHAROM: U11.46 (~CHAROM); also elsewhere on the board
~CS_CIA1: U3.11 (O4); also elsewhere on the board
~CS_CIA2: U3.10 (O5); also elsewhere on the board
~CS_COLRAM: U11.45 (~COLRAM); also elsewhere on the board
~CS_FROM: U11.33 (~FROM); also elsewhere on the board
~CS_IO1: U3.9 (O6); also elsewhere on the board
~CS_IO2: U3.7 (O7); also elsewhere on the board
~CS_ROM1: U11.37 (~ROM_1); also elsewhere on the board
~CS_ROM2: U11.36 (~ROM_2); also elsewhere on the board
~CS_ROM3: U11.35 (~ROM_3); also elsewhere on the board
~CS_ROM4: U11.34 (~ROM_4); also elsewhere on the board
~CS_ROMH: U11.31 (~ROMH); also elsewhere on the board
~CS_ROML: U11.30 (~ROML); also elsewhere on the board
~CS_SID: U3.15 (O0); also elsewhere on the board
~CS_VIC: U11.42 (~VIC); also elsewhere on the board
~RESET: U7.2 (~RESET); also elsewhere on the board

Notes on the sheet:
Open: 128k ROM Close: 256k ROM
Close: Enable CAS latch
